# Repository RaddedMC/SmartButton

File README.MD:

# RaddedMC's SmartButton
This project is currently a work-in-progress. Most things work but there are a few small things to be ironed out...
Requirements:
 - An ESP32 or ESP8266 Microcontroller
 - An internet connection / WiFi router
 - Some webhooks!
 - Some kind of button -- the PCB is designed for a stanard 6x6mm tactile switch
 - Also helpful to have an LED and/or passive piezo -- the PCB is designed for a Murata PKMCS0909E4000-R1
 - Two resistors; values will vary, but the schematic has a 220 and 320 ohm. Use a resistor appropriate for your LED
 
Instructions:
 - Build the below circuit:
 
   - If you're using an ESP8266 NodeMCU, substitute D2, D4, and D6 with the pins labelled D4, D2, and D1 respectively. The LED resistor is 320 ohm and the button pulldown resistor is 220 ohm, however, these are not strict values
   - **OR** use the PCB in the PCB folder, credits to kelvinhall05 for the design!
 - Clone the EasyButton.ino file that matches your board
 - Make sure your Arduino IDE is set up for an ESP32 or ESP8266 NodeMCU board
 - Set Wifi SSID and password, and set up webhooks of your choosing (make sure that you use http:// in your URL as opposed to https://. 
 - You can change pins to whatever you like. Helpful if you want the ESP's built-in LED to blink when you do things or if you want to use one of the touch sensor pins instead of a boring clicky button. Pinout is currently configured for both boards to be compatible with one PCB.
 
**As mentioned, this project is a work in progress. Suggestions are appreciated, and these instructions might change over time.**

Feel free to dm me on Insta @RaddedMC or Discord at RaddedMC#4791 for any questions. Video for this project is in the works!

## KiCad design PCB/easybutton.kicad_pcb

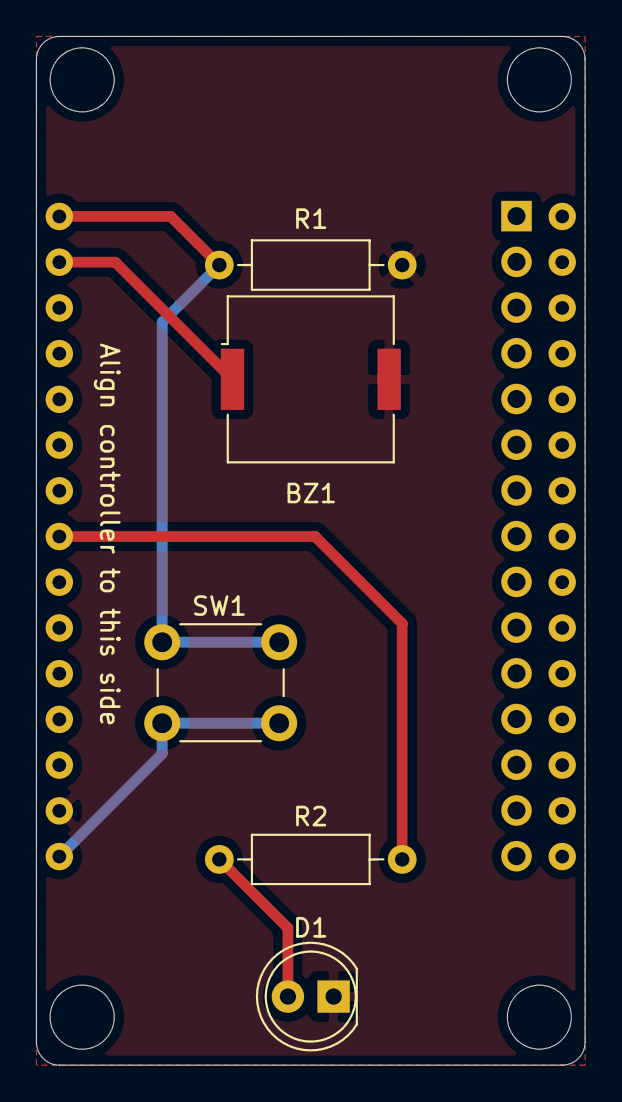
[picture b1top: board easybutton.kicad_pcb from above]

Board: 2 copper layers, 30.5 x 57.2 mm, 6 parts (1 on the bottom side), 6 nets.

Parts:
BZ1: Buzzer; Buzzer_Murata_PKMCS0909E4000-R1
D1: LED; LED_D5.0mm
R1: 220; R_Axial_DIN0207_L6.3mm_D2.5mm_P10.16mm_Horizontal
R2: 320; R_Axial_DIN0207_L6.3mm_D2.5mm_P10.16mm_Horizontal
SW1: Speaker button; SW_PUSH_6mm
U1: NodeMCU1.0(ESP-12E); NodeMCU-LoLinV3

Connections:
Button: R1.2, SW1.1, U1.30
Buzzer: BZ1.1, U1.29
GND: BZ1.2, D1.1, R1.1, U1.17
LED: R2.2, U1.23
unnamed: D1.2, R2.1
VCC: SW1.2, U1.16

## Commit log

2020-10-25 First Commit Current code DOES work but I'd like to make some changes
2020-10-25 v1.1 -- Small updates Made LED and piezo react at the same moment rather than one before the other, making the SmartButton experience more responsive. Change the serial baud rate to the normal 115200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
2020-10-25 Removed an unused variable
2020-10-25 Added ESP8266 support! Also added a wiring diagram. Other changes have probably occurred as well.
2020-10-25 Changed some readme formatting
2020-11-07 Pinout change for PCB I think this is the second time I've changed the 'default' pins for this project, but the new pinout that I've selected will use the same physical location on both the ESP8266 a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
2020-11-07 Added a PCB!
    PCB design credit to u/kelvinh_27. This PCB can be edited in kicad and should contain files that most fabs can accept for production.
2020-11-17 removed a thing
2020-12-05 Small update For some reason after a long period of inactivity if I were to click my own personal SmartButton it would fail every time, and then work after a second press. Not exactly sure what's cau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
2020-12-05 Deleted file
2021-03-28 Updating PCB, regenerating gerbers
2021-03-28 Updating PCB and readme
2021-03-28 Updating readme
